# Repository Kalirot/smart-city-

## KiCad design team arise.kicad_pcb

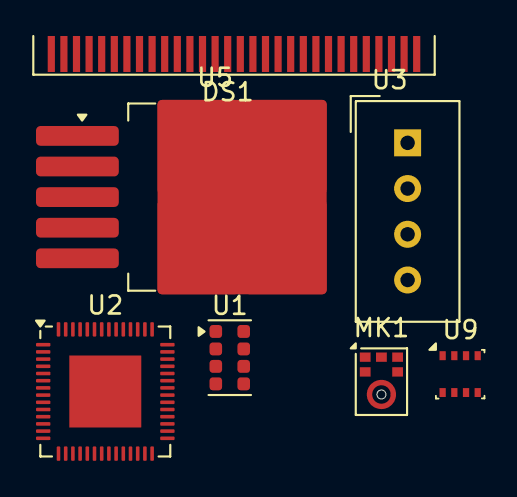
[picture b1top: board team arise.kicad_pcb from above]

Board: 2 copper layers, 7 parts (0 on the bottom side), 10 nets, no tracks yet.

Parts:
DS1: OLED-128O064D
MK1: ICS-43434; InvenSense_ICS-43434-6_3.5x2.65mm
U1: RPR-0521RS; Rohm_RPR-0521RS
U2: ESP32-S3; QFN-56-1EP_7x7mm_P0.4mm_EP4x4mm
U3: DHT11; Aosong_DHT11_5.5x12.0_P2.54mm
U5: LM2576HVS-3.3; TO-263-5_TabPin3
U9: BME280; Bosch_LGA-8_2.5x2.5mm_P0.65mm_ClockwisePinNumbering

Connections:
unnamed: DS1.5 (C1N), U2.27 (GPIO21), U9.3 (SDI)
unnamed: DS1.2 (C2N), U2.22 (XTAL_32K_N), U2.52 (GPIO46)
unnamed: DS1.1 (GND), DS1.28 (VCC), DS1.30 (GND), MK1.3 (GND), U1.1 (VDD), U1.3 (GND), U2.2 (VDD3P3), U2.3 (VDD3P3), U2.28 (SPICS1), U2.55 (VDDA), U2.56 (VDDA), U2.57 (GND), U3.1 (VDD), U3.4 (GND), U5.1 (VIN), U5.5 (~ON/OFF), U9.6 (VDDIO), U9.7 (GND), U9.8 (VDD)
unnamed: U2.25 (GPIO19/USB_D-), U2.33 (SPICLK), U3.2 (DATA)
unnamed: U2.41 (GPIO36), U9.4 (SCK)
unnamed: U1.8 (SDA), U2.23 (GPIO17), U2.44 (MTCK)
unnamed: MK1.2 (LR), U2.40 (GPIO35)
unnamed: MK1.5 (VDD), U2.20 (VDD3P3_RTC)
unnamed: U1.2 (SCL), U2.13 (GPIO8)
unnamed: U5.2 (OUT), U5.4 (FB)
